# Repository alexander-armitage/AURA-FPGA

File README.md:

<div align="center">

# AURA-FPGA

This repository is a project currently under development to make an Artix-7 FPGA based System on Module (SOM).

</div>

### Introduction

> **TODO** Write an introduction.

### PCB Design

> **TODO** Document PCB design, pin-out, and hardware user-guide.

### Vivado

> **TODO** Document block diagram design for pinout validation and to eventually run Petalinux.

> **TODO** Document IP configurations and notes (specifically MIG).

> **TODO** Document tcl build process.

### Petalinux

> **TODO** This is where any files/setup related to Petalinux will go.

### Software

> **TODO** This is where any bare metal microblaze code for Vitis will go.

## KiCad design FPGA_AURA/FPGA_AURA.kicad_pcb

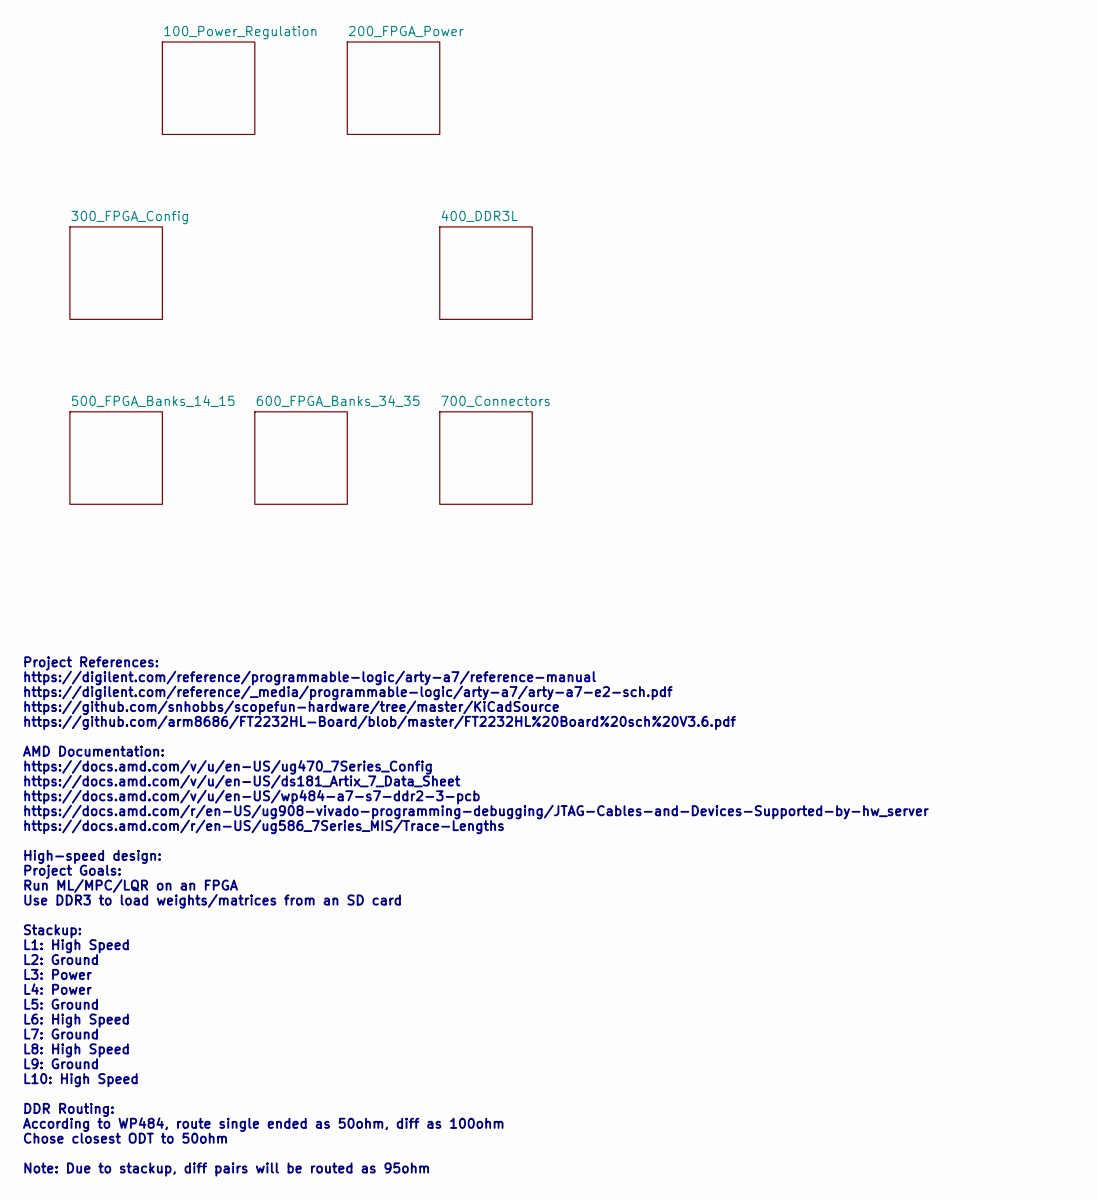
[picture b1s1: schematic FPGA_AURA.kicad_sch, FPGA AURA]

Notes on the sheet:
Project References: https://digilent.com/reference/programmable-logic/arty-a7/reference-manual https://digilent.com/reference/_media/programmable-logic/arty-a7/arty-a7-e2-sch.pdf https://github.com/snhobbs/scopefun-hardware/tree/master/KiCadSource https://github.com/arm8686/FT2232HL-Board/blob/mast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

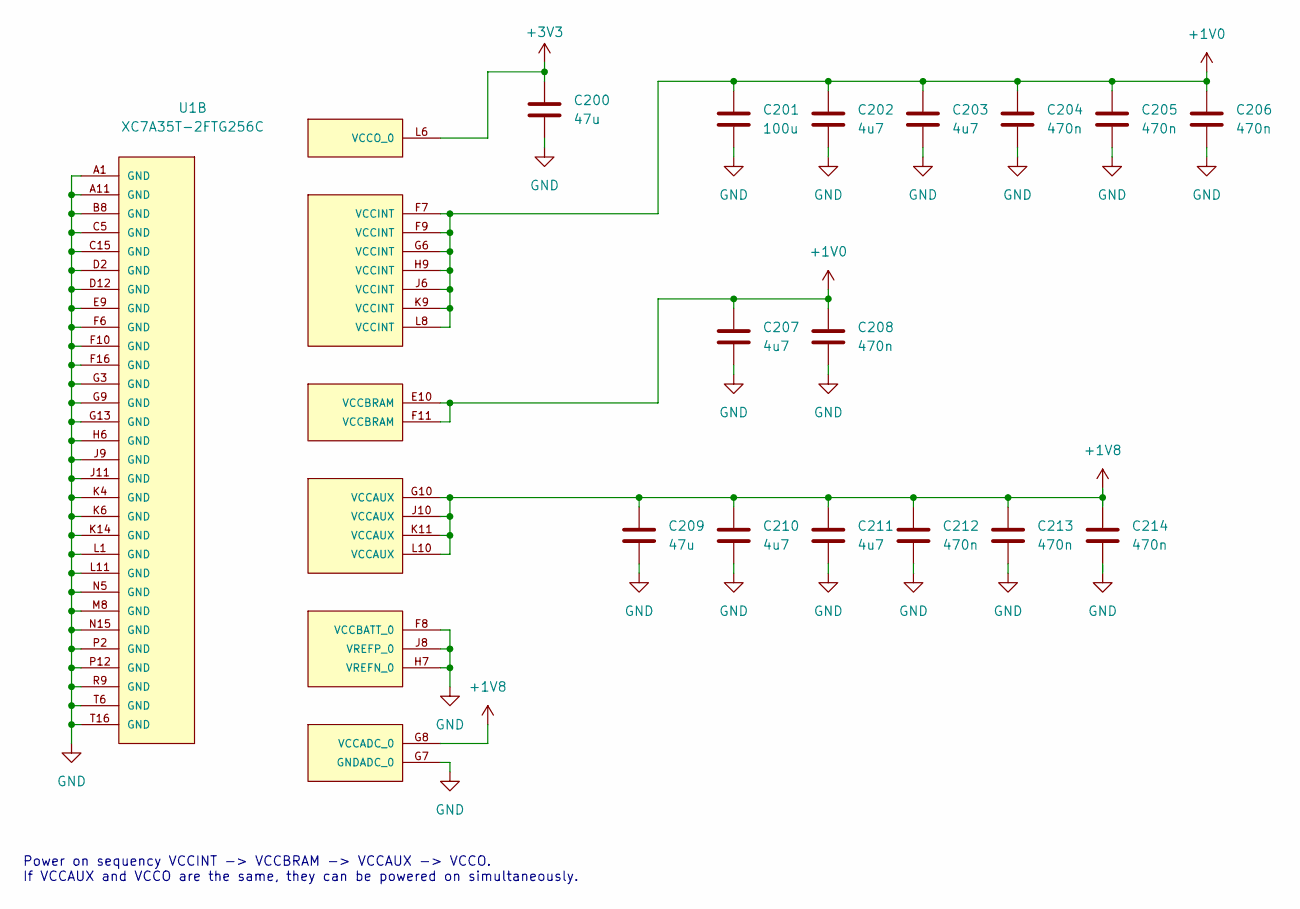
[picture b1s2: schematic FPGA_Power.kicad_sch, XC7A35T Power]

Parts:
C200, C209: 47u; C_0603_1608Metric
C201: 100u; C_0805_2012Metric
C202, C203, C207, C210, C211: 4u7; C_0603_1608Metric
C204, C205, C206, C208, C212, C213, C214: 470n; C_0402_1005Metric
U1: XC7A35T-2FTG256C; BGA256C100P16X16_1700X1700X155

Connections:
+1V0: C201.1, C202.1, C203.1, C204.1, C205.1, C206.1, C207.1, C208.1, U1.E10 (VCCBRAM), U1.F7 (VCCINT), U1.F9 (VCCINT), U1.F11 (VCCBRAM), U1.G6 (VCCINT), U1.H9 (VCCINT), U1.J6 (VCCINT), U1.K9 (VCCINT), U1.L8 (VCCINT); also elsewhere on the board
+1V8: C209.1, C210.1, C211.1, C212.1, C213.1, C214.1, U1.G8 (VCCADC_0), U1.G10 (VCCAUX), U1.J10 (VCCAUX), U1.K11 (VCCAUX), U1.L10 (VCCAUX); also elsewhere on the board
+3V3: C200.1, U1.L6 (VCCO_0); also elsewhere on the board
GND: C200.2, C201.2, C202.2, C203.2, C204.2, C205.2, C206.2, C207.2, C208.2, C209.2, C210.2, C211.2, C212.2, C213.2, C214.2, U1.A1 (GND), U1.A11 (GND), U1.B8 (GND), U1.C5 (GND), U1.C15 (GND), U1.D2 (GND), U1.D12 (GND), U1.E9 (GND), U1.F6 (GND), U1.F8 (VCCBATT_0), U1.F10 (GND), U1.F16 (GND), U1.G3 (GND), U1.G7 (GNDADC_0), U1.G9 (GND), U1.G13 (GND), U1.H6 (GND), U1.H7 (VREFN_0), U1.J8 (VREFP_0), U1.J9 (GND), U1.J11 (GND), U1.K4 (GND), U1.K6 (GND), U1.K14 (GND), U1.L1 (GND), U1.L11 (GND), U1.M8 (GND), U1.N5 (GND), U1.N15 (GND), U1.P2 (GND), U1.P12 (GND), U1.R9 (GND), U1.T6 (GND), U1.T16 (GND); also elsewhere on the board

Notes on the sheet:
Power on sequency VCCINT -> VCCBRAM -> VCCAUX -> VCCO. If VCCAUX and VCCO are the same, they can be powered on simultaneously.

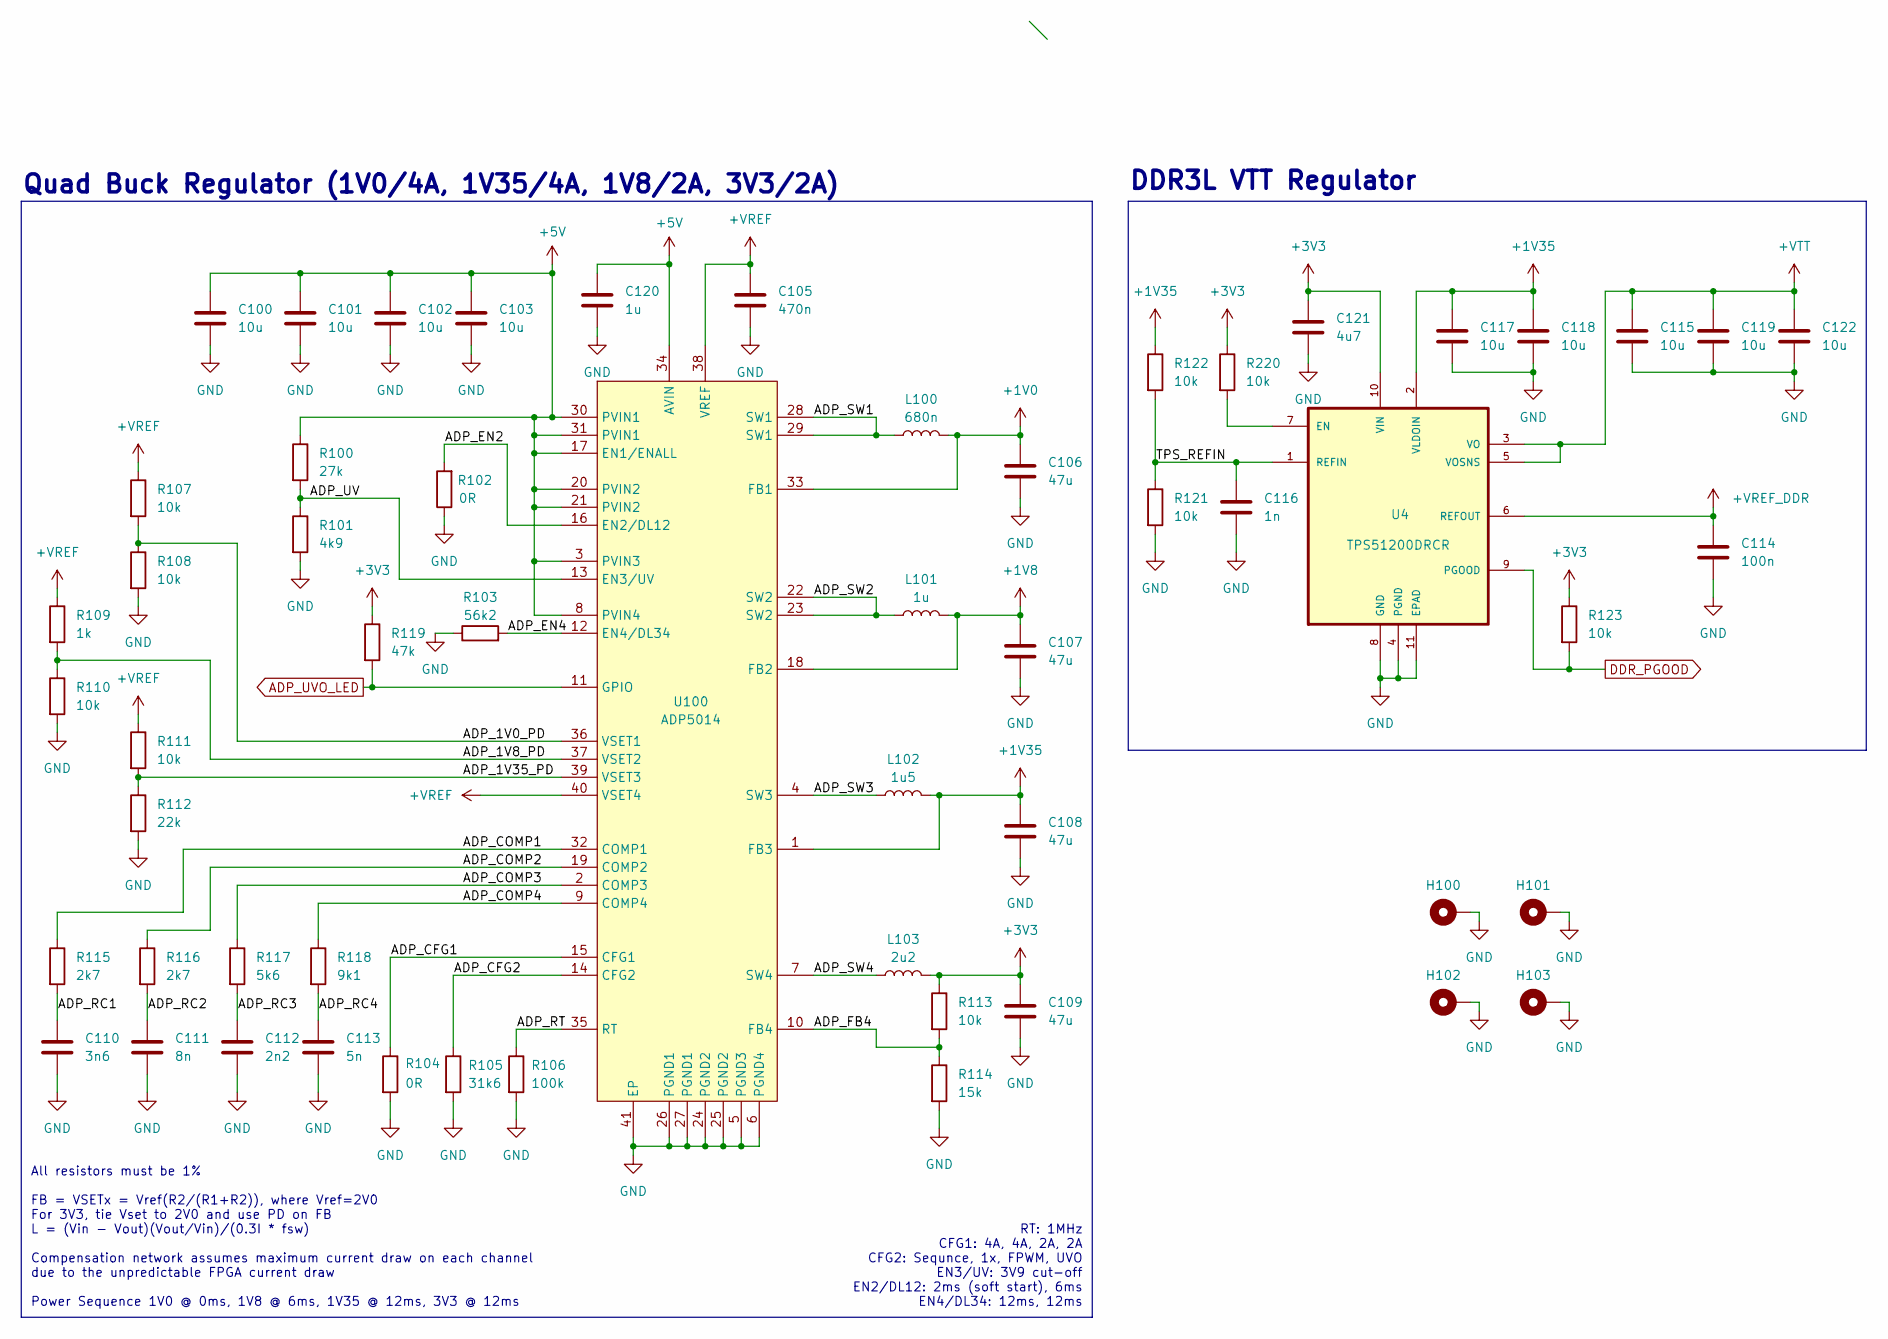
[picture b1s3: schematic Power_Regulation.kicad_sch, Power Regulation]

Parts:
C100, C101, C102, C103: 10u; C_0603_1608Metric
C105: 470n; C_0402_1005Metric
C106, C107, C108, C109: 47u; C_0805_2012Metric
C110: 3n6; C_0402_1005Metric
C111: 8n; C_0402_1005Metric
C112: 2n2; C_0402_1005Metric
C113: 5n; C_0402_1005Metric
C114: 100n; C_0402_1005Metric
C115, C117, C118, C119, C122: 10u; C_0402_1005Metric
C116: 1n; C_0402_1005Metric
C120: 1u; C_0402_1005Metric
C121: 4u7; C_0402_1005Metric
H100, H101, H102, H103: MountingHole_Pad; MountingHole_3.2mm_M3_Pad_Via
L100: 680n; L_Chilisin_BMRB00050518-B
L101: 1u; L_Chilisin_BMRB00050518-B
L102: 1u5; L_1008_2520Metric
L103: 2u2; L_1008_2520Metric
R100: 27k; R_0402_1005Metric
R101: 4k9; R_0402_1005Metric
R102, R104: 0R; R_0402_1005Metric
R103: 56k2; R_0402_1005Metric
R105: 31k6; R_0402_1005Metric
R106: 100k; R_0402_1005Metric
R107, R108, R110, R111, R113, R121, R122, R123, R220: 10k; R_0402_1005Metric
R109: 1k; R_0402_1005Metric
R112: 22k; R_0402_1005Metric
R114: 15k; R_0402_1005Metric
R115, R116: 2k7; R_0402_1005Metric
R117: 5k6; R_0402_1005Metric
R118: 9k1; R_0402_1005Metric
R119: 47k; R_0402_1005Metric
U4: TPS51200DRCR; VREG_V62_16624-01YE
U100: ADP5014; QFN50P600X600X80-41N430X430

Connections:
+1V0: C106.1, L100.2, U100.33 (FB1); also elsewhere on the board
+1V8: C107.1, L101.2, U100.18 (FB2); also elsewhere on the board
+1V35: C108.1, C117.1, C118.1, L102.2, R122.1, U4.2 (VLDOIN), U100.1 (FB3); also elsewhere on the board
+3V3: C109.1, C121.1, L103.2, R113.1, R119.1, R123.1, R220.1, U4.10 (VIN); also elsewhere on the board
+5V: C100.1, C101.1, C102.1, C103.1, C120.1, R100.1, U100.3 (PVIN3), U100.8 (PVIN4), U100.17 (EN1/ENALL), U100.20 (PVIN2), U100.21 (PVIN2), U100.30 (PVIN1), U100.31 (PVIN1), U100.34 (AVIN); also elsewhere on the board
+VREF: C105.1, R107.1, R109.1, R111.1, U100.38 (VREF), U100.40 (VSET4)
+VREF_DDR: C114.1, U4.6 (REFOUT); also elsewhere on the board
+VTT: C115.1, C119.1, C122.1, U4.3 (VO), U4.5 (VOSNS); also elsewhere on the board
/100_Power_Regulation/ADP_1V0_PD: R107.2, R108.1, U100.36 (VSET1)
/100_Power_Regulation/ADP_1V8_PD: R109.2, R110.1, U100.37 (VSET2)
/100_Power_Regulation/ADP_1V35_PD: R111.2, R112.1, U100.39 (VSET3)
/100_Power_Regulation/ADP_CFG1: R104.1, U100.15 (CFG1)
/100_Power_Regulation/ADP_CFG2: R105.1, U100.14 (CFG2)
/100_Power_Regulation/ADP_COMP1: R115.1, U100.32 (COMP1)
/100_Power_Regulation/ADP_COMP2: R116.1, U100.19 (COMP2)
/100_Power_Regulation/ADP_COMP3: R117.1, U100.2 (COMP3)
/100_Power_Regulation/ADP_COMP4: R118.1, U100.9 (COMP4)
/100_Power_Regulation/ADP_EN2: R102.2, U100.16 (EN2/DL12)
/100_Power_Regulation/ADP_EN4: R103.2, U100.12 (EN4/DL34)
/100_Power_Regulation/ADP_FB4: R113.2, R114.1, U100.10 (FB4)
/100_Power_Regulation/ADP_RC1: C110.1, R115.2
/100_Power_Regulation/ADP_RC2: C111.1, R116.2
/100_Power_Regulation/ADP_RC3: C112.1, R117.2
/100_Power_Regulation/ADP_RC4: C113.1, R118.2
/100_Power_Regulation/ADP_RT: R106.1, U100.35 (RT)
/100_Power_Regulation/ADP_SW1: L100.1, U100.28 (SW1), U100.29 (SW1)
/100_Power_Regulation/ADP_SW2: L101.1, U100.22 (SW2), U100.23 (SW2)
/100_Power_Regulation/ADP_SW3: L102.1, U100.4 (SW3)
/100_Power_Regulation/ADP_SW4: L103.1, U100.7 (SW4)
/100_Power_Regulation/ADP_UV: R100.2, R101.1, U100.13 (EN3/UV)
/100_Power_Regulation/TPS_REFIN: C116.1, R121.1, R122.2, U4.1 (REFIN)
ADP_UVO_LED: R119.2, U100.11 (GPIO)
DDR_PGOOD: R123.2, U4.9 (PGOOD)
GND: C100.2, C101.2, C102.2, C103.2, C105.2, C106.2, C107.2, C108.2, C109.2, C110.2, C111.2, C112.2, C113.2, C114.2, C115.2, C116.2, C117.2, C118.2, C119.2, C120.2, C121.2, C122.2, H100.1 (1_1), H101.1 (1_1), H102.1 (1_1), H103.1 (1_1), R101.2, R102.1, R103.1, R104.2, R105.2, R106.2, R108.2, R110.2, R112.2, R114.2, R121.2, U4.4 (PGND), U4.8 (GND), U4.11 (EPAD), U100.5 (PGND3), U100.6 (PGND4), U100.24 (PGND2), U100.25 (PGND2), U100.26 (PGND1), U100.27 (PGND1), U100.41 (EP); also elsewhere on the board
unnamed: R220.2, U4.7 (EN)

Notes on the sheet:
DDR3L VTT Regulator
Quad Buck Regulator (1V0/4A, 1V35/4A, 1V8/2A, 3V3/2A)
All resistors must be 1% FB = VSETx = Vref(R2/(R1+R2)), where Vref=2V0 For 3V3, tie Vset to 2V0 and use PD on FB L = (Vin - Vout)(Vout/Vin)/(0.3I * fsw) Compensation network assumes maximum current draw on each channel due to the unpredictable FPGA current draw Power Sequence 1V0 @ 0ms, 1V8 @ 6ms, 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
RT: 1MHz CFG1: 4A, 4A, 2A, 2A CFG2: Sequnce, 1x, FPWM, UVO EN3/UV: 3V9 cut-off EN2/DL12: 2ms (soft start), 6ms EN4/DL34: 12ms, 12ms

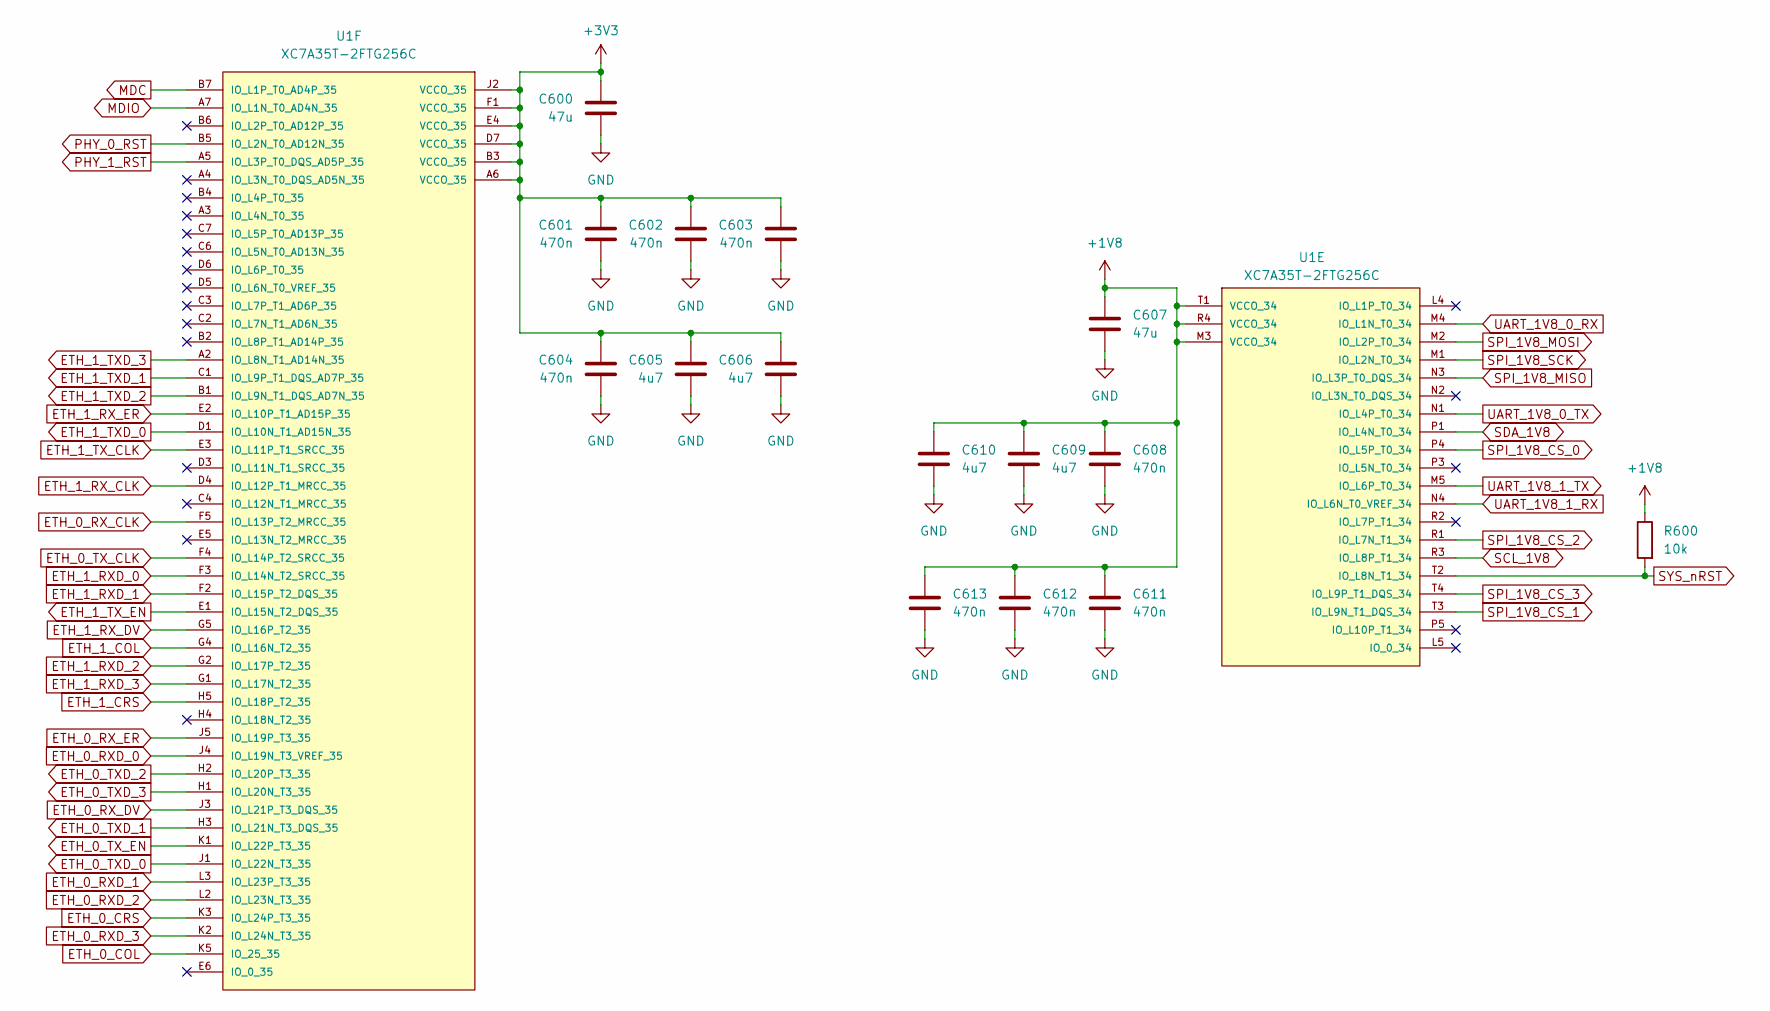
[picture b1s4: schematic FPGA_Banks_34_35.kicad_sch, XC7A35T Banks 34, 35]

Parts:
C600, C607: 47u; C_0603_1608Metric
C601, C602, C603, C604, C608, C611, C612, C613: 470n; C_0402_1005Metric
C605, C606, C609, C610: 4u7; C_0603_1608Metric
R600: 10k; R_0402_1005Metric
U1: XC7A35T-2FTG256C; BGA256C100P16X16_1700X1700X155

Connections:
+1V8: C607.1, C608.1, C609.1, C610.1, C611.1, C612.1, C613.1, R600.1, U1.M3 (VCCO_34), U1.R4 (VCCO_34), U1.T1 (VCCO_34); also elsewhere on the board
+3V3: C600.1, C601.1, C602.1, C603.1, C604.1, C605.1, C606.1, U1.A6 (VCCO_35), U1.B3 (VCCO_35), U1.D7 (VCCO_35), U1.E4 (VCCO_35), U1.F1 (VCCO_35), U1.J2 (VCCO_35); also elsewhere on the board
ETH_0_COL: U1.K5 (IO_25_35); also elsewhere on the board
ETH_0_CRS: U1.K3 (IO_L24P_T3_35); also elsewhere on the board
ETH_0_RXD_0: U1.J4 (IO_L19N_T3_VREF_35); also elsewhere on the board
ETH_0_RXD_1: U1.L3 (IO_L23P_T3_35); also elsewhere on the board
ETH_0_RXD_2: U1.L2 (IO_L23N_T3_35); also elsewhere on the board
ETH_0_RXD_3: U1.K2 (IO_L24N_T3_35); also elsewhere on the board
ETH_0_RX_CLK: U1.F5 (IO_L13P_T2_MRCC_35); also elsewhere on the board
ETH_0_RX_DV: U1.J3 (IO_L21P_T3_DQS_35); also elsewhere on the board
ETH_0_RX_ER: U1.J5 (IO_L19P_T3_35); also elsewhere on the board
ETH_0_TXD_0: U1.J1 (IO_L22N_T3_35); also elsewhere on the board
ETH_0_TXD_1: U1.H3 (IO_L21N_T3_DQS_35); also elsewhere on the board
ETH_0_TXD_2: U1.H2 (IO_L20P_T3_35); also elsewhere on the board
ETH_0_TXD_3: U1.H1 (IO_L20N_T3_35); also elsewhere on the board
ETH_0_TX_CLK: U1.F4 (IO_L14P_T2_SRCC_35); also elsewhere on the board
ETH_0_TX_EN: U1.K1 (IO_L22P_T3_35); also elsewhere on the board
ETH_1_COL: U1.G4 (IO_L16N_T2_35); also elsewhere on the board
ETH_1_CRS: U1.H5 (IO_L18P_T2_35); also elsewhere on the board
ETH_1_RXD_0: U1.F3 (IO_L14N_T2_SRCC_35); also elsewhere on the board
ETH_1_RXD_1: U1.F2 (IO_L15P_T2_DQS_35); also elsewhere on the board
ETH_1_RXD_2: U1.G2 (IO_L17P_T2_35); also elsewhere on the board
ETH_1_RXD_3: U1.G1 (IO_L17N_T2_35); also elsewhere on the board
ETH_1_RX_CLK: U1.D4 (IO_L12P_T1_MRCC_35); also elsewhere on the board
ETH_1_RX_DV: U1.G5 (IO_L16P_T2_35); also elsewhere on the board
ETH_1_RX_ER: U1.E2 (IO_L10P_T1_AD15P_35); also elsewhere on the board
ETH_1_TXD_0: U1.D1 (IO_L10N_T1_AD15N_35); also elsewhere on the board
ETH_1_TXD_1: U1.C1 (IO_L9P_T1_DQS_AD7P_35); also elsewhere on the board
ETH_1_TXD_2: U1.B1 (IO_L9N_T1_DQS_AD7N_35); also elsewhere on the board
ETH_1_TXD_3: U1.A2 (IO_L8N_T1_AD14N_35); also elsewhere on the board
ETH_1_TX_CLK: U1.E3 (IO_L11P_T1_SRCC_35); also elsewhere on the board
ETH_1_TX_EN: U1.E1 (IO_L15N_T2_DQS_35); also elsewhere on the board
GND: C600.2, C601.2, C602.2, C603.2, C604.2, C605.2, C606.2, C607.2, C608.2, C609.2, C610.2, C611.2, C612.2, C613.2; also elsewhere on the board
MDC: U1.B7 (IO_L1P_T0_AD4P_35); also elsewhere on the board
MDIO: U1.A7 (IO_L1N_T0_AD4N_35); also elsewhere on the board
PHY_0_RST: U1.B5 (IO_L2N_T0_AD12N_35); also elsewhere on the board
PHY_1_RST: U1.A5 (IO_L3P_T0_DQS_AD5P_35); also elsewhere on the board
SCL_1V8: U1.R3 (IO_L8P_T1_34); also elsewhere on the board
SDA_1V8: U1.P1 (IO_L4N_T0_34); also elsewhere on the board
SPI_1V8_CS_0: U1.P4 (IO_L5P_T0_34); also elsewhere on the board
SPI_1V8_CS_1: U1.T3 (IO_L9N_T1_DQS_34); also elsewhere on the board
SPI_1V8_CS_2: U1.R1 (IO_L7N_T1_34); also elsewhere on the board
SPI_1V8_CS_3: U1.T4 (IO_L9P_T1_DQS_34); also elsewhere on the board
SPI_1V8_MISO: U1.N3 (IO_L3P_T0_DQS_34); also elsewhere on the board
SPI_1V8_MOSI: U1.M2 (IO_L2P_T0_34); also elsewhere on the board
SPI_1V8_SCK: U1.M1 (IO_L2N_T0_34); also elsewhere on the board
SYS_nRST: R600.2, U1.T2 (IO_L8N_T1_34); also elsewhere on the board
UART_1V8_0_RX: U1.M4 (IO_L1N_T0_34); also elsewhere on the board
UART_1V8_0_TX: U1.N1 (IO_L4P_T0_34); also elsewhere on the board
UART_1V8_1_RX: U1.N4 (IO_L6N_T0_VREF_34); also elsewhere on the board
UART_1V8_1_TX: U1.M5 (IO_L6P_T0_34); also elsewhere on the board

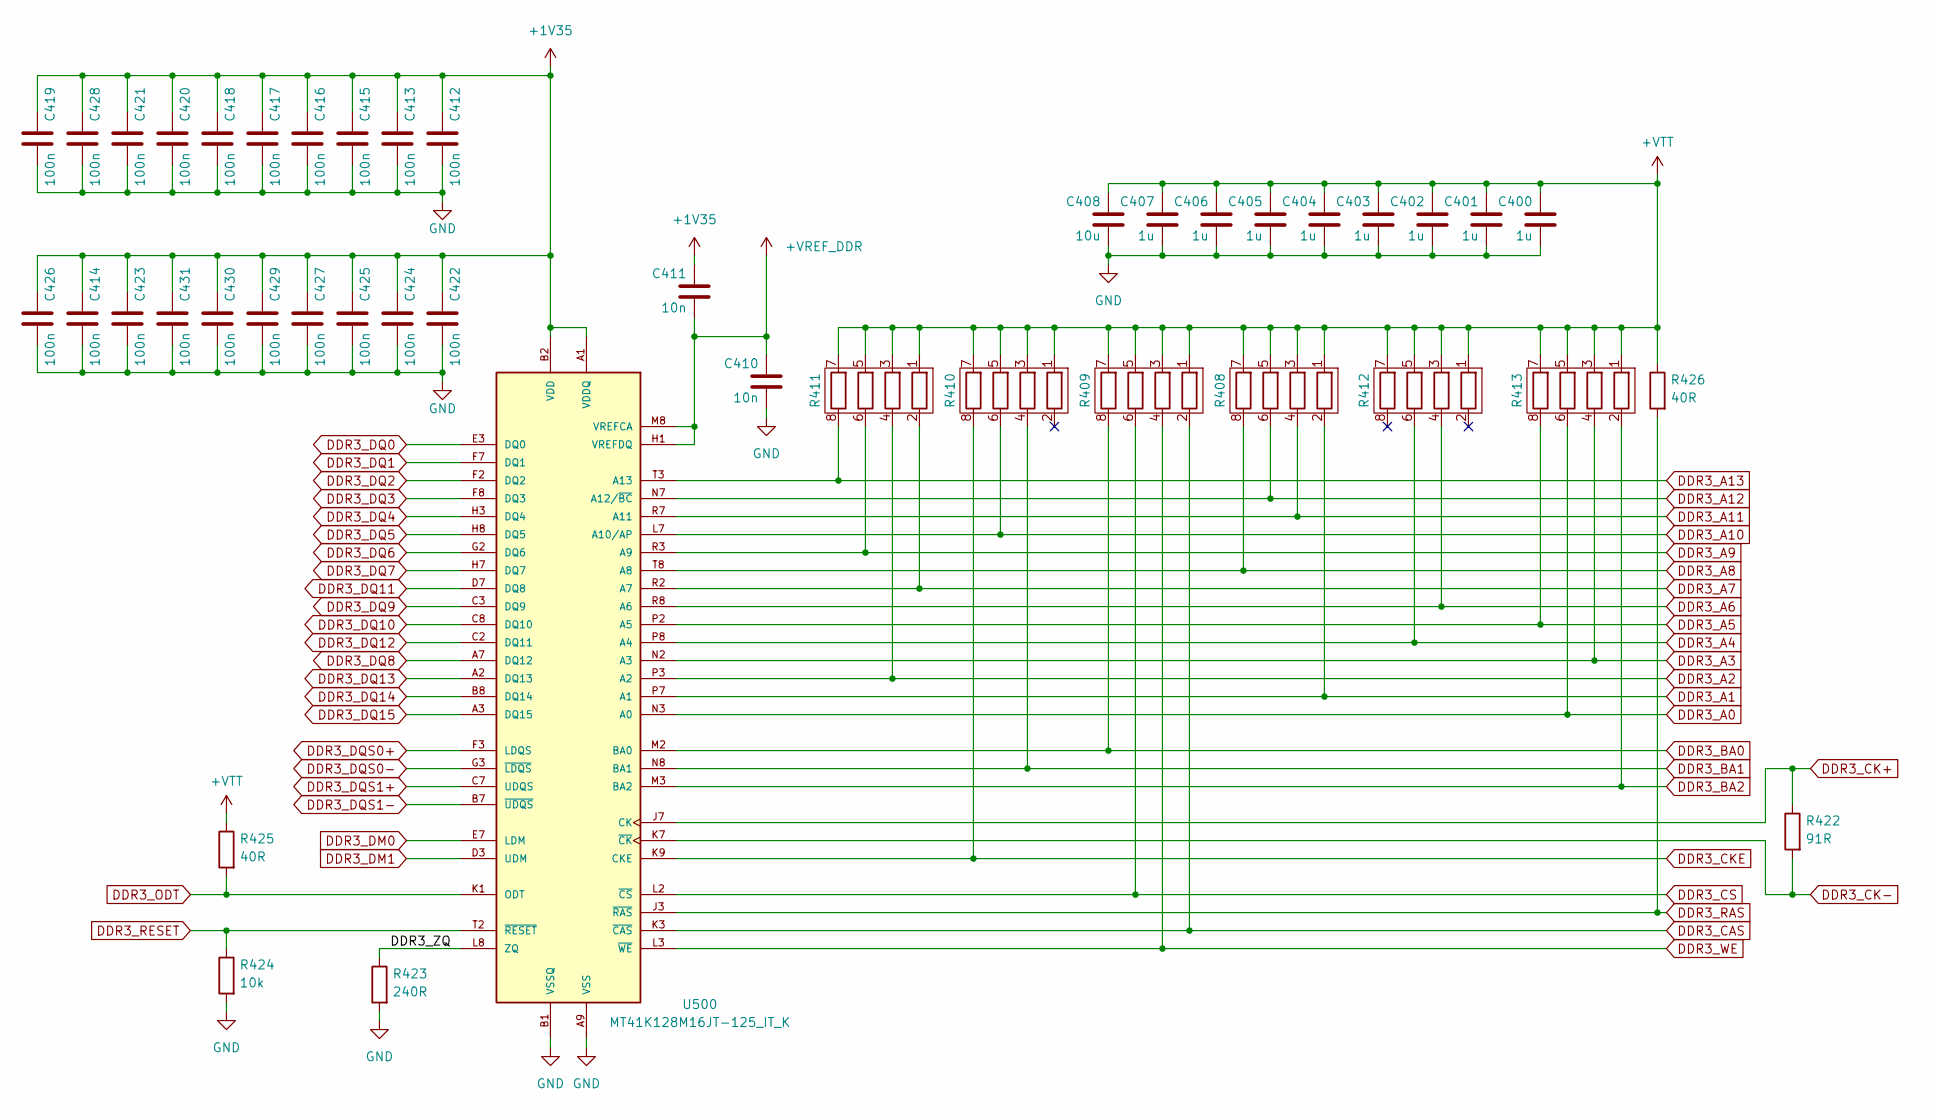
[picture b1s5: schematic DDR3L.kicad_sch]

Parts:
C400, C401, C402, C403, C404, C405, C406, C407: 1u; C_0402_1005Metric
C408: 10u; C_0402_1005Metric
C410, C411: 10n; C_0402_1005Metric
C412, C413, C417, C421, C422, C431: 100n; C_0402_1005Metric
C414, C415, C416, C418, C419, C420, C423, C424, C425, C426, C427, C428, C429, C430: 100n; C_0201_0603Metric
R408, R409, R410, R411, R412, R413: 40R2; 0402_4
R422: 91R; R_0201_0603Metric
R423: 240R; R_0402_1005Metric
R424: 10k; R_0402_1005Metric
R425, R426: 40R; R_0201_0603Metric
U500: MT41K128M16JT-125_IT_K; BGA80P96C6X16_800X1400X110

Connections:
+1V35: C411.1, C412.1, C413.1, C414.1, C415.1, C416.1, C417.1, C418.1, C419.1, C420.1, C421.1, C422.1, C423.1, C424.1, C425.1, C426.1, C427.1, C428.1, C429.1, C430.1, C431.1, U500.A1 (VDDQ), U500.A8 (VDDQ), U500.B2 (VDD), U500.C1 (VDDQ), U500.C9 (VDDQ), U500.D2 (VDDQ), U500.D9 (VDD), U500.E9 (VDDQ), U500.F1 (VDDQ), U500.G7 (VDD), U500.H2 (VDDQ), U500.H9 (VDDQ), U500.K2 (VDD), U500.K8 (VDD), U500.N1 (VDD), U500.N9 (VDD), U500.R1 (VDD), U500.R9 (VDD); also elsewhere on the board
+VREF_DDR: C410.1, C411.2, U500.H1 (VREFDQ), U500.M8 (VREFCA); also elsewhere on the board
+VTT: C400.1, C401.1, C402.1, C403.1, C404.1, C405.1, C406.1, C407.1, C408.1, R408.1, R408.3, R408.5, R408.7, R409.1, R409.3, R409.5, R409.7, R410.1, R410.3, R410.5, R410.7, R411.1, R411.3, R411.5, R411.7, R412.1, R412.3, R412.5, R412.7, R413.1, R413.3, R413.5, R413.7, R425.1, R426.1; also elsewhere on the board
/400_DDR3L/DDR3_ZQ: R423.1, U500.L8 (ZQ)
DDR3_A0: R413.6, U500.N3 (A0); also elsewhere on the board
DDR3_A1: R408.2, U500.P7 (A1); also elsewhere on the board
DDR3_A2: R411.4, U500.P3 (A2); also elsewhere on the board
DDR3_A3: R413.4, U500.N2 (A3); also elsewhere on the board
DDR3_A4: R412.6, U500.P8 (A4); also elsewhere on the board
DDR3_A5: R413.8, U500.P2 (A5); also elsewhere on the board
DDR3_A6: R412.4, U500.R8 (A6); also elsewhere on the board
DDR3_A7: R411.2, U500.R2 (A7); also elsewhere on the board
DDR3_A8: R408.8, U500.T8 (A8); also elsewhere on the board
DDR3_A9: R411.6, U500.R3 (A9); also elsewhere on the board
DDR3_A10: R410.6, U500.L7 (A10/AP); also elsewhere on the board
DDR3_A11: R408.4, U500.R7 (A11); also elsewhere on the board
DDR3_A12: R408.6, U500.N7 (A12/~BC); also elsewhere on the board
DDR3_A13: R411.8, U500.T3 (A13); also elsewhere on the board
DDR3_BA0: R409.8, U500.M2 (BA0); also elsewhere on the board
DDR3_BA1: R410.4, U500.N8 (BA1); also elsewhere on the board
DDR3_BA2: R413.2, U500.M3 (BA2); also elsewhere on the board
DDR3_CAS: R409.2, U500.K3 (~CAS); also elsewhere on the board
DDR3_CK+: R422.1, U500.J7 (CK); also elsewhere on the board
DDR3_CK-: R422.2, U500.K7 (~CK); also elsewhere on the board
DDR3_CKE: R410.8, U500.K9 (CKE); also elsewhere on the board
DDR3_CS: R409.6, U500.L2 (~CS); also elsewhere on the board
DDR3_DM0: U500.E7 (LDM); also elsewhere on the board
DDR3_DM1: U500.D3 (UDM); also elsewhere on the board
DDR3_DQ0: U500.E3 (DQ0); also elsewhere on the board
DDR3_DQ1: U500.F7 (DQ1); also elsewhere on the board
DDR3_DQ2: U500.F2 (DQ2); also elsewhere on the board
DDR3_DQ3: U500.F8 (DQ3); also elsewhere on the board
DDR3_DQ4: U500.H3 (DQ4); also elsewhere on the board
DDR3_DQ5: U500.H8 (DQ5); also elsewhere on the board
DDR3_DQ6: U500.G2 (DQ6); also elsewhere on the board
DDR3_DQ7: U500.H7 (DQ7); also elsewhere on the board
DDR3_DQ8: U500.A7 (DQ12); also elsewhere on the board
DDR3_DQ9: U500.C3 (DQ9); also elsewhere on the board
DDR3_DQ10: U500.C8 (DQ10); also elsewhere on the board
DDR3_DQ11: U500.D7 (DQ8); also elsewhere on the board
DDR3_DQ12: U500.C2 (DQ11); also elsewhere on the board
DDR3_DQ13: U500.A2 (DQ13); also elsewhere on the board
DDR3_DQ14: U500.B8 (DQ14); also elsewhere on the board
DDR3_DQ15: U500.A3 (DQ15); also elsewhere on the board
DDR3_DQS0+: U500.F3 (LDQS); also elsewhere on the board
DDR3_DQS0-: U500.G3 (~LDQS); also elsewhere on the board
DDR3_DQS1+: U500.C7 (UDQS); also elsewhere on the board
DDR3_DQS1-: U500.B7 (~UDQS); also elsewhere on the board
DDR3_ODT: R425.2, U500.K1 (ODT); also elsewhere on the board
DDR3_RAS: R426.2, U500.J3 (~RAS); also elsewhere on the board
DDR3_RESET: R424.1, U500.T2 (~RESET); also elsewhere on the board
DDR3_WE: R409.4, U500.L3 (~WE); also elsewhere on the board
GND: C400.2, C401.2, C402.2, C403.2, C404.2, C405.2, C406.2, C407.2, C408.2, C410.2, C412.2, C413.2, C414.2, C415.2, C416.2, C417.2, C418.2, C419.2, C420.2, C421.2, C422.2, C423.2, C424.2, C425.2, C426.2, C427.2, C428.2, C429.2, C430.2, C431.2, R423.2, R424.2, U500.A9 (VSS), U500.B1 (VSSQ), U500.B3 (VSS), U500.B9 (VSSQ), U500.D1 (VSSQ), U500.D8 (VSSQ), U500.E1 (VSS), U500.E2 (VSSQ), U500.E8 (VSSQ), U500.F9 (VSSQ), U500.G1 (VSSQ), U500.G8 (VSS), U500.G9 (VSSQ), U500.J2 (VSS), U500.J8 (VSS), U500.M1 (VSS), U500.M9 (VSS), U500.P1 (VSS), U500.P9 (VSS), U500.T1 (VSS), U500.T9 (VSS); also elsewhere on the board
